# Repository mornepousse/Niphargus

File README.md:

<p align="center">
  <picture>
    <source media="(prefers-color-scheme: dark)" srcset="images/niphargus_logo_white.svg">
    
  </picture>
</p>

<h1 align="center">Niphargus</h1>

<p align="center">
  <em>The cave shrimp: blind, discreet, indestructible.</em><br>
  <em>La crevette des cavernes : aveugle, discrète, indestructible.</em>
</p>

---

## English

Niphargus is a thin, unkillable wireless split keyboard.

- **Two self-contained halves** — one ESP32-S3-WROOM-1 + nRF24L01+ and a 16340
  cell each, matrix scanning in deep sleep (RTC domain), the
  [KeSp dongle](https://github.com/mornepousse/KeSp_dongle) on the host side.
- **Wired fallback** — direct USB-C plus a TRRS jack between halves: *plugging it
  back in must be enough*. A 5 V handshake on the link makes hot-plug spark-free.
- **ESD hardening throughout** — TVS diodes on USB and TRRS, 100 Ω in series on
  every matrix line, careful ground planes. The static discharge you bring back
  to the keyboard will no longer crash it.
- **Sharp Memory LCD** (right half) for layer and battery status: holds its image
  at a few µA and never flickers. **Azoteq TPS43 trackpad** (left half), over I²C.
- **The survival kit** — an ESP32-P4 vault behind a CH334R USB hub: multi-ISO boot
  key, PGP token, storage. It only powers up when the keyboard is plugged in.

A complete redesign of the **Rouge-Gorge** (v1, 2022), a Jorne / Kyria rev2
derivative that was never built. This repository carries the full history:
Rouge-Gorge → rili → Niphargus.

**Status (2026-08)** — v2 schematic complete and reviewed, board routed, ERC and
DRC clean. Case in progress (see below). Firmware to follow.

## Français

Niphargus est un clavier split sans fil, fin et increvable.

- **Deux moitiés autonomes** — ESP32-S3-WROOM-1 + nRF24L01+ et une batterie 16340
  chacune, scan de la matrice en sommeil profond (domaine RTC),
  [dongle KeSp](https://github.com/mornepousse/KeSp_dongle) côté hôte.
- **Repli filaire** — USB-C direct et jack TRRS entre les moitiés : *rebrancher
  doit suffire*. Une poignée de main 5 V sur le lien évite les étincelles au branchement à chaud.
- **Robustesse ESD partout** — TVS sur USB et TRRS, 100 Ω série sur chaque ligne
  de matrice, plans de masse soignés. La décharge que vous ramenez au clavier ne
  le plantera plus.
- **Écran Sharp Memory LCD** (moitié droite) pour le calque et l'état des batteries :
  tient l'image à quelques µA sans jamais clignoter. **Trackpad Azoteq TPS43**
  (moitié gauche), en I²C.
- **La trousse de secours** — un coffre ESP32-P4 derrière un hub USB CH334R : clé
  bootable multi-ISO, token PGP, stockage. Il ne s'allume qu'en filaire.

Refonte complète du **Rouge-Gorge** (v1, 2022), un dérivé du Jorne et du Kyria
rev2 resté sur le papier. Le dépôt porte tout l'historique :
Rouge-Gorge → rili → Niphargus.

**État (2026-08)** — schéma v2 terminé et relu, carte routée, ERC et DRC au vert.
Boîtier en cours (ci-dessous). Firmware à suivre.

---

## Repository layout · Organisation du dépôt

| Path | Contents |
|---|---|
| `hardware/pcb/` | KiCad project — `niphar.kicad_pro` (schematic, board, footprints) |
| `hardware/order-*.csv` | Part orders: TME, LCSC, AliExpress |
| `hardware/kit-jlcpcb/` | Gerbers, BOM and CPL for JLCPCB |
| `case/` | Case generator and CAD output |
| `scripts/` | Anti-regression checks |
| `docs/` | Design specs and plans |

### Case · Boîtier

Three parts: a **CNC-machined 8.5 mm aluminium frame**, sandwiched between two
**2 mm polycarbonate plates**, 12.5 mm overall. The 16340 cell sits *beside* the
board, in a pocket milled into the frame itself.

Trois pièces : un **cadre aluminium usiné de 8,5 mm** pris entre deux **plaques
polycarbonate de 2 mm**, 12,5 mm hors tout. La 16340 se loge *à côté* de la carte,
dans une poche fraisée à même le cadre.

The frame outline is **not computed — it is drawn**. Edit `case/case_outline.svg`
(KiCad coordinates, 1 unit = 1 mm), then run:

Le contour du cadre n'est **pas calculé, il est dessiné**. Éditez
`case/case_outline.svg` (repère KiCad, 1 unité = 1 mm), puis lancez :

```sh
freecad --console case/gen_case.py
```

This regenerates the `.FCStd`, the STEP, the STL files and `case_plan.svg`.

### Anti-regression · Anti-régression

```sh
./scripts/check.sh --fast   # schematic ERC against the committed baseline
./scripts/check.sh          # + full board DRC
./scripts/install-hooks.sh  # once per clone: pre-push runs the full check
```

Green means *never more ERC/DRC errors or warnings than the committed baseline*
(`.tripwire-kicad-baseline`). CI is pinned to KiCad 10.0.4 with its own reference.

Vert signifie *jamais plus d'erreurs ni de warnings ERC/DRC que la référence
committée*. La CI est épinglée sur KiCad 10.0.4 avec sa propre référence.

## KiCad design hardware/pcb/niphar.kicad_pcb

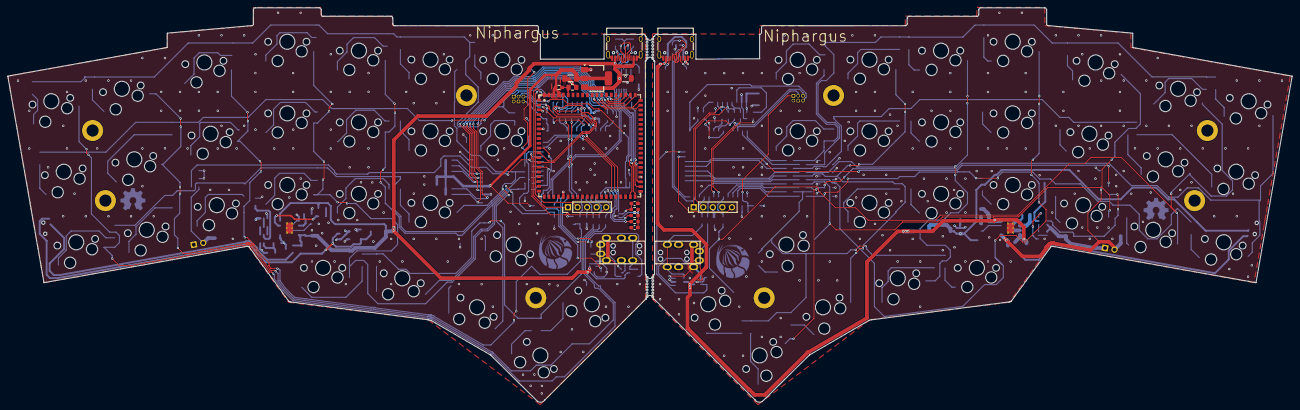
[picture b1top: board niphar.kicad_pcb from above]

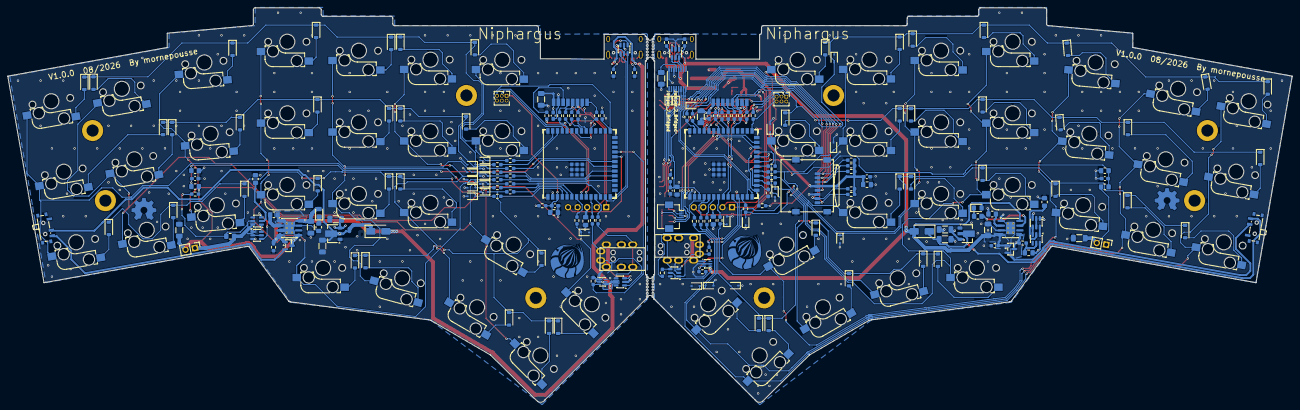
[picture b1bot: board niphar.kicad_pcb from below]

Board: 4 copper layers, 340.8 x 104.7 mm, 283 parts (206 on the bottom side), 208 nets.

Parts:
C1, C2, C5, C6, C7, C8, C17, C21, C22: 100nF; C_0603_1608Metric_Pad1.08x0.95mm_HandSolder
C3, C4, C9, C10, C14, C18, C27, C28: 1uF; C_0805_2012Metric_Pad1.18x1.45mm_HandSolder
C11, C12, C13, C15, C16, C19, C20, C23, C24, C25, C26, C29, C30: 10uF; C_1206_3216Metric_Pad1.33x1.80mm_HandSolder
D1, D2, D3, D4, D5, D6, D7, D8, D9, D10, D11, D12, D13, D14, D15, D16, D17, D18, D19, D20, D21, D22, D23, D24, D25, D26, D27, D28, D29, D30, D31, D32, D33, D34, D35, D36, D37, D38, D39, D40, D41, D42, D43, D44, D45, D46, D47, D48: D; D_SOD-123
D49, D50: LED; LED_0805_2012Metric_Pad1.15x1.40mm_HandSolder
D51, D52: SS14; D_SMA
D100, D101, D102, D103, D104, D105, D106, D107, D108, D109, D110, D111, D112, D113, D114, D115, D116, D117, D118, D119, D120, D121: SD05C-01F; D_SOD-323
H1, H2, H3, H4, H5, H6, H7, H8: MountingHole_Pad_MP; MountingHole_3.2mm_M3_DIN965_Pad
HS1, HS2: Heatsink_Pad; Niphargus_10mm_Cu
HS3: Heatsink_Pad; Niphargus_text_3mm_silk
J1, J2: Conn_02x03_Odd_Even; PinHeader_2x03_P1.27mm_Vertical
J3: TPS43_FPC; Hirose_FH12-6S-0.5SH_1x06-1MP_P0.50mm_Horizontal
J4, J12: Conn_01x05_Pin; PinHeader_1x05_P2.54mm_Vertical
J5, J6: AudioJack4; MJ-4PP-9_rev3
J7, J8: USB_C_Receptacle_USB2.0_16P; USB_C_Receptacle_HRO_TYPE-C-31-M-12
J9: Micro_SD_Card; microSD_HC_Wuerth_693072010801
J10, J11: Battery; PinHeader_1x02_P2.54mm_Vertical
JP1, JP2: Jumper_2_Bridged; Jumper
Q1, Q2: AO3407; SOT-23
Q3, Q4: FS8205; SOT-23-6
R1, R2, R33, R34, R48, R49, R54, R55, R56, R57, R58, R59: 10k; R_0603_1608Metric_Pad0.98x0.95mm_HandSolder
R3, R4, R5, R6, R7, R8, R9, R10, R11, R12, R13, R14, R15, R16, R17, R18, R19, R20, R21, R22, R23, R24, R25, R26, R27, R28, R30, R31, R36, R37, R38, R39, R40, R41, R44, R45, R46, R47, R70, R71: 100; R_0603_1608Metric_Pad0.98x0.95mm_HandSolder
R29, R32: 4.7k; R_0603_1608Metric_Pad0.98x0.95mm_HandSolder
R35, R42, R43, R60, R61: 100k; R_0603_1608Metric_Pad0.98x0.95mm_HandSolder
R50, R51, R52, R53: 5k1; R_0603_1608Metric_Pad0.98x0.95mm_HandSolder
R62, R63, R72, R73: 1k; R_0805_2012Metric_Pad1.20x1.40mm_HandSolder
R64, R65, R66, R67: 1M; R_0805_2012Metric_Pad1.20x1.40mm_HandSolder
R68, R69: 2k4; R_0805_2012Metric_Pad1.20x1.40mm_HandSolder
SW1, SW2, SW3, SW4, SW5, SW6, SW7, SW8, SW9, SW10, SW11, SW12, SW13, SW14, SW15, SW16, SW17, SW18, SW19, SW20, SW21, SW22, SW23, SW24, SW25, SW26, SW27, SW28, SW29, SW30, SW31, SW32, SW33, SW34, SW35, SW36, SW37, SW38, SW39, SW40, SW41, SW42, SW43, SW44, SW45, SW46, SW47, SW48, SW49, SW50, SW51, SW52: SW_PUSH; SW_Cherry_MX_1.00u_PCB
SW53, SW54: SW_SPDT; SW_SPDT_PCM12
U1, U2, U3, U4: D; D_SOD-123
U5, U6: ESP32-S3-WROOM-1; ESP32-S3-WROOM-1U
U7, U8: NRF24L01_Breakout; NRF24L01
U9, U10: SRV05-4; SOT-23-6
U11, U12: SiP32431DR3; SOT-363_SC-70-6
U13: CH334R; QSOP-16_3.9x4.9mm_P0.635mm
U14, U15: USBLC6-2SC6; SOT-23-6
U16: ESP32P4_QFN104; JC-ESP32P4-M3_V0.2
U17: AMS1117-3.3; SOT-223-3_TabPin2
U18, U19: TP4056-42-ESOP8; SOIC-8-1EP_3.9x4.9mm_P1.27mm_EP2.41x3.3mm_ThermalVias
U20, U21: HT7833; SOT-89-3
U22, U23: DW01A; SOT-23-6

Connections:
+3.3V: C6.1, C8.2, C9.2, C11.2, C26.2, J1.2, J3.4, J12.3, R2.2, R29.1, R32.1, R34.2, R35.1, U6.2 (3V3), U8.2 (VCC), U20.3 (VO)
+3.3V_D: C7.2, C10.2, C12.2, C25.2, J2.2, J4.3, R1.2, R33.2, U5.2 (3V3), U7.2 (VCC), U21.3 (VO)
+5V: C15.2, C20.2, D49.2 (A), D52.2 (A), J8.A4 (VBUS), J8.A9 (VBUS), J8.B4 (VBUS), J8.B9 (VBUS), Q2.1 (G), R60.2, U9.5 (VP), U12.4 (IN), U13.12 (V5), U14.5 (VBUS), U17.3 (VI), U18.4 (V_{CC}), U18.8 (CE)
+5V_D: C19.2, D50.2 (A), D51.2 (A), J7.A4 (VBUS), J7.A9 (VBUS), J7.B4 (VBUS), J7.B9 (VBUS), Q1.1 (G), R61.2, U10.5 (VP), U11.4 (IN), U15.5 (VBUS), U19.4 (V_{CC}), U19.8 (CE)
+BATT: C29.1, J10.2, Q2.3 (D), R64.1, R70.1, U18.5 (BAT)
+BATT_D: C30.1, J11.2, Q1.3 (D), R65.1, R71.1, U19.5 (BAT)
-BATT: C27.2, J10.1, Q4.1 (S1), U23.6 (GND)
-BATT_D: C28.2, J11.1, Q3.1 (S1), U22.6 (GND)
/P4/P4_3V3: C16.2, C17.2, C18.2, J9.4 (VDD), R48.2, R54.2, R55.1, R56.1, R57.1, R58.1, R59.1, U16.77 (ESP_3V3), U16.78 (ESP_3V3), U17.2 (VO)
/P4/SD_CLK: J9.5 (CLK), U16.63 (GPIO43)
/P4/SD_CMD: J9.3 (CMD), R57.2, U16.64 (GPIO44)
/P4/SD_DATA0: J9.7 (DAT0), R58.2, U16.59 (GPIO39)
/P4/SD_DATA1: J9.8 (DAT1), R59.2, U16.60 (GPIO40)
/P4/SD_DATA2: J9.1 (DAT2), R55.2, U16.61 (GPIO41)
/P4/SD_DATA3: J9.2 (DAT3/CD), R56.2, U16.62 (GPIO42)
/USB/DPU+: U13.11 (DPU+), U14.4 (I/O2)
/USB/DPU-: U13.10 (DMU-), U14.6 (I/O1)
/right/CE_1: R38.1, U5.8 (GPIO15/U0RTS/ADC2_CH4/XTAL_32K_P)
/right/CSN_1: R37.1, U5.9 (GPIO16/U0CTS/ADC2_CH5/XTAL_32K_N)
/right/CS_DPL: J4.5, U5.22 (GPIO14/TOUCH14/ADC2_CH3/FSPIWP/FSPIDQS/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)
/right/EN: C2.2, C4.2, J2.1, R1.1, U5.3 (EN)
/right/IO0: J2.6, R33.1, U5.27 (GPIO0/BOOT)
/right/IRQ_1: R40.1, U5.34 (MTDI/GPIO41/CLK_OUT1)
/right/LINK_5V_EN: R43.1, U5.23 (GPIO21), U11.3 (ON)
/right/LINK_RX: R44.2, U5.11 (GPIO18/U1RXD/ADC2_CH7/CLK_OUT3)
/right/LINK_TX: R46.2, U5.10 (GPIO17/U1TXD/ADC2_CH6)
/right/MISO: R15.2, U7.7 (MISO)
/right/MOSI: J4.1, R17.2, U7.6 (MOSI)
/right/RX: J2.5, U5.36 (U0RXD/GPIO44/CLK_OUT2)
/right/SCK: J4.2, R31.2, U7.5 (SCK)
/right/TIP_5V: J5.T, U10.3 (IO2), U11.1 (OUT)
/right/TX: J2.3, U5.37 (U0TXD/GPIO43/CLK_OUT1)
/right/col0: R12.2, U5.6 (GPIO6/TOUCH6/ADC1_CH5)
/right/col1: R13.2, U5.7 (GPIO7/TOUCH7/ADC1_CH6)
/right/col2: R19.2, U5.12 (GPIO8/TOUCH8/ADC1_CH7/SUBSPICS1)
/right/col3: R22.2, U5.17 (GPIO9/TOUCH9/ADC1_CH8/FSPIHD/SUBSPIHD)
/right/col4: R24.2, U5.19 (GPIO11/TOUCH11/ADC2_CH0/FSPID/FSPIIO5/S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)
/right/col5: R26.2, U5.18 (GPIO10/TOUCH10/ADC1_CH9/FSPICS0/FSPIIO4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)
/right/col6: R28.2, U5.39 (GPIO1/TOUCH1/ADC1_CH0)
/right/row0: R3.1, U5.38 (GPIO2/TOUCH2/ADC1_CH1)
/right/row1: R5.1, U5.20 (GPIO12/TOUCH12/ADC2_CH1/FSPICLK/FSPIIO6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)
/right/row2: R8.1, U5.4 (GPIO4/TOUCH4/ADC1_CH3)
/right/row3: R10.1, U5.5 (GPIO5/TOUCH5/ADC1_CH4)
/s3/CE_1: R39.1, U6.8 (GPIO15/U0RTS/ADC2_CH4/XTAL_32K_P)
/s3/CSN_1: R36.1, U6.9 (GPIO16/U0CTS/ADC2_CH5/XTAL_32K_N)
/s3/CS_DPL: J12.5, U6.22 (GPIO14/TOUCH14/ADC2_CH3/FSPIWP/FSPIDQS/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)
/s3/EN: C1.2, C3.2, J1.1, R2.1, U6.3 (EN)
/s3/IO0: J1.6, R34.1, U6.27 (GPIO0/BOOT)
/s3/IRQ_1: R41.1, U6.34 (MTDI/GPIO41/CLK_OUT1)
/s3/LINK_5V_EN: R42.1, U6.23 (GPIO21), U12.3 (ON)
/s3/LINK_RX: R45.2, U6.11 (GPIO18/U1RXD/ADC2_CH7/CLK_OUT3)
/s3/LINK_TX: R47.2, U6.10 (GPIO17/U1TXD/ADC2_CH6)
/s3/RX: J1.5, U6.36 (U0RXD/GPIO44/CLK_OUT2)
/s3/TIP_5V: J6.T, U9.3 (IO2), U12.1 (OUT)
/s3/TP_NRST: C5.1, J3.2, R35.2
/s3/TP_RDY: J3.1, U6.35 (MTMS/GPIO42)
/s3/TP_SCL: J3.5, R32.2, U6.25 (GPIO48/SPICLK_N/SUBSPICLK_N_DIFF)
/s3/TP_SDA: J3.6, R29.2, U6.24 (GPIO47/SPICLK_P/SUBSPICLK_P_DIFF)
/s3/TX: J1.3, U6.37 (U0TXD/GPIO43/CLK_OUT1)
/s3/col0: R11.2, U6.4 (GPIO4/TOUCH4/ADC1_CH3)
/s3/col1: R14.2, U6.5 (GPIO5/TOUCH5/ADC1_CH4)
/s3/col2: R20.2, U6.7 (GPIO7/TOUCH7/ADC1_CH6)
/s3/col3: R21.2, U6.17 (GPIO9/TOUCH9/ADC1_CH8/FSPIHD/SUBSPIHD)
/s3/col4: R23.2, U6.18 (GPIO10/TOUCH10/ADC1_CH9/FSPICS0/FSPIIO4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)
/s3/col5: R25.2, U6.19 (GPIO11/TOUCH11/ADC2_CH0/FSPID/FSPIIO5/S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)
/s3/col6: R27.2, U6.20 (GPIO12/TOUCH12/ADC2_CH1/FSPICLK/FSPIIO6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)
/s3/row0: R4.1, U6.39 (GPIO1/TOUCH1/ADC1_CH0)
/s3/row1: R6.1, U6.38 (GPIO2/TOUCH2/ADC1_CH1)
/s3/row2: R7.1, U6.12 (GPIO8/TOUCH8/ADC1_CH7/SUBSPICS1)
/s3/row3: R9.1, U6.6 (GPIO6/TOUCH6/ADC1_CH5)
CS_P4: R48.1, U6.15 (GPIO3/TOUCH3/ADC1_CH2), U16.11 (GPIO7)
D+_p4: U13.6 (DP2+), U16.40 (ESP_USB_P)
D+_s3: U6.14 (GPIO20/U1CTS/ADC2_CH9/CLK_OUT1/USB_D+), U13.8 (DP1+)
D+_s3_d: U5.14 (GPIO20/U1CTS/ADC2_CH9/CLK_OUT1/USB_D+), U15.4 (I/O2)
D-_p4: U13.5 (DM2-), U16.39 (ESP_USB_N)
D-_s3: U6.13 (GPIO19/U1RTS/ADC2_CH8/CLK_OUT2/USB_D-), U13.7 (DM1-)
D-_s3_d: U5.13 (GPIO19/U1RTS/ADC2_CH8/CLK_OUT2/USB_D-), U15.6 (I/O1)
GND: C1.1, C2.1, C3.1, C4.1, C5.2, C6.2, C7.1, C8.1, C9.1, C10.1, C11.1, C12.1, C13.2, C14.1, C15.1, C16.1, C17.1, C18.1, C19.1, C20.1, C21.1, C22.1, C23.1, C24.1, C25.1, C26.1, C29.2, C30.2, D100.2 (A2), D101.2 (A2), D102.2 (A2), D103.2 (A2), D104.2 (A2), D105.2 (A2), D106.2 (A2), D107.1 (A1), D108.1 (A1), D109.1 (A1), D110.1 (A1), D111.2 (A2), D112.2 (A2), D113.2 (A2), D114.2 (A2), D115.2 (A2), D116.2 (A2), D117.2 (A2), D118.2 (A2), D119.2 (A2), D120.2 (A2), D121.2 (A2), J1.4, J2.4, J3.3, J4.4, J5.S, J6.S, J7.A1 (GND), J7.A12 (GND), J7.B1 (GND), J7.B12 (GND), J7.SH (SHIELD), J8.A1 (GND), J8.A12 (GND), J8.B1 (GND), J8.B12 (GND), J8.SH (SHIELD), J9.6 (VSS), J9.SH (SHIELD), J12.4, Q3.3 (S2), Q4.3 (S2), R42.2, R43.2, R49.1, R50.2, R51.2, R52.1, R53.1, R60.1, R61.1, R66.2, R67.2, R68.2, R69.2, R72.2, R73.2, U5.1 (GND), U5.40 (GND), U5.41 (GND), U6.1 (GND), U6.40 (GND), U6.41 (GND), U7.1 (GND), U8.1 (GND), U9.2 (VN), U10.2 (VN), U11.2 (GND), U11.5 (GND), U12.2 (GND), U12.5 (GND), U13.14 (GND), U13.16 (XI), U14.2 (GND), U15.2 (GND), U16.1 (GND), U16.3 (GND), U16.7 (GND), U16.25 (GND), U16.32 (GND), U16.41 (GND), U16.44 (GND), U16.79 (GND), U16.80 (GND), U17.1 (GND), U18.1 (TEMP), U18.3 (GND), U18.9 (EPAD), U19.1 (TEMP), U19.3 (GND), U19.9 (EPAD), U20.1 (GND), U21.1 (GND)
IRQ_P4: R49.2, U6.16 (GPIO46), U16.15 (GPIO11)
J_PROG_P4_N: JP2.2 (B), U13.3 (DM3-)
J_PROG_P4_P: JP1.2 (B), U13.4 (DP3+)
MISO_L: R16.2, U8.7 (MISO), U16.14 (GPIO10)
MOSI_L: J12.1, R18.2, U8.6 (MOSI), U16.12 (GPIO8)
unnamed: D1.2 (A), SW2.2
unnamed: D1.1 (K), D10.1 (K), D15.1 (K), D22.1 (K), D29.1 (K), D37.1 (K), D45.1 (K), D118.1 (A1), R3.2
unnamed: D2.2 (A), SW1.2
unnamed: D3.2 (A), SW3.2
unnamed: D4.2 (A), SW4.2
unnamed: D5.2 (A), SW6.2
unnamed: D6.2 (A), SW5.2
unnamed: D7.2 (A), SW7.2
unnamed: D8.2 (A), SW8.2
unnamed: D9.2 (A), SW10.2
unnamed: D10.2 (A), SW9.2
unnamed: D11.2 (A), SW12.2
unnamed: D12.2 (A), SW11.2
unnamed: D13.2 (A), SW14.2
unnamed: D14.2 (A), SW13.2
unnamed: D15.2 (A), SW18.2
unnamed: D16.2 (A), SW17.2
unnamed: D17.2 (A), SW20.2
unnamed: D18.2 (A), SW19.2
unnamed: D19.2 (A), SW22.2
unnamed: D20.2 (A), SW21.2
unnamed: D21.2 (A), SW26.2
unnamed: D22.2 (A), SW25.2
unnamed: D23.2 (A), SW28.2
unnamed: D24.2 (A), SW27.2
unnamed: D25.2 (A), SW29.2
unnamed: D26.2 (A), SW30.2
unnamed: D27.2 (A), SW32.2
unnamed: D28.2 (A), SW31.2
unnamed: D29.2 (A), SW34.2
unnamed: D30.2 (A), SW33.2
unnamed: D31.2 (A), SW36.2
unnamed: D32.2 (A), SW35.2
unnamed: D33.2 (A), SW38.2
unnamed: D34.2 (A), SW37.2
unnamed: D35.2 (A), SW39.2
unnamed: D36.2 (A), SW40.2
unnamed: D37.2 (A), SW42.2
unnamed: D38.2 (A), SW41.2
unnamed: D39.2 (A), SW44.2
unnamed: D40.2 (A), SW43.2
unnamed: D41.2 (A), SW45.2
unnamed: D42.2 (A), SW46.2
unnamed: D43.2 (A), SW47.2
unnamed: D44.2 (A), SW48.2
unnamed: D45.2 (A), SW50.2
unnamed: D46.2 (A), SW49.2
unnamed: D47.2 (A), SW51.2
unnamed: D48.2 (A), SW52.2
unnamed: D49.1 (K), R62.1
unnamed: D50.1 (K), R63.1
unnamed: C23.2, D51.1 (K), SW53.2 (B), U21.2 (VI)
unnamed: C24.2, D52.1 (K), SW54.3 (C), U20.2 (VI)
unnamed: D100.1 (A1), R11.1, SW1.1, SW3.1, SW5.1, SW8.1
unnamed: D101.1 (A1), R14.1, SW10.1, SW12.1, SW14.1, SW15.1
unnamed: D102.1 (A1), R20.1, SW17.1, SW19.1, SW21.1, SW24.1
unnamed: D103.1 (A1), R21.1, SW26.1, SW27.1, SW30.1, SW31.1
unnamed: D104.1 (A1), R23.1, SW33.1, SW35.1, SW38.1, SW40.1
unnamed: D105.1 (A1), R25.1, SW41.1, SW43.1, SW45.1, SW47.1
unnamed: D106.1 (A1), R27.1, SW49.1, SW52.1
unnamed: D2.1 (K), D9.1 (K), D16.1 (K), D21.1 (K), D30.1 (K), D38.1 (K), D46.1 (K), D107.2 (A2), R4.2
unnamed: D3.1 (K), D11.1 (K), D18.1 (K), D24.1 (K), D32.1 (K), D40.1 (K), D48.1 (K), D108.2 (A2), R6.2
unnamed: D6.1 (K), D13.1 (K), D20.1 (K), D26.1 (K), D33.1 (K), D41.1 (K), D109.2 (A2), R7.2
unnamed: D8.1 (K), D28.1 (K), D36.1 (K), D43.1 (K), D110.2 (A2), R9.2, U2.1 (K), U3.1 (K)
unnamed: D111.1 (A1), R12.1, SW2.1, SW4.1, SW6.1, SW7.1
unnamed: D112.1 (A1), R13.1, SW9.1, SW11.1, SW13.1, SW16.1
unnamed: D113.1 (A1), R19.1, SW18.1, SW20.1, SW22.1, SW23.1
unnamed: D114.1 (A1), R22.1, SW25.1, SW28.1, SW29.1, SW32.1
unnamed: D115.1 (A1), R24.1, SW34.1, SW36.1, SW37.1, SW39.1
unnamed: D116.1 (A1), R26.1, SW42.1, SW44.1, SW46.1, SW48.1
unnamed: D117.1 (A1), R28.1, SW50.1, SW51.1
unnamed: D4.1 (K), D12.1 (K), D17.1 (K), D23.1 (K), D31.1 (K), D39.1 (K), D47.1 (K), D119.1 (A1), R5.2
unnamed: D5.1 (K), D14.1 (K), D19.1 (K), D25.1 (K), D34.1 (K), D42.1 (K), D120.1 (A1), R8.2
unnamed: D7.1 (K), D27.1 (K), D35.1 (K), D44.1 (K), D121.1 (A1), R10.2, U1.1 (K), U4.1 (K)
unnamed: J7.A5 (CC1), R51.1
unnamed: J7.B5 (CC2), R53.2
unnamed: J7.A6 (D+), J7.B6 (D+), U15.3 (I/O2)
unnamed: J7.A7 (D-), J7.B7 (D-), U15.1 (I/O1)
unnamed: J8.A5 (CC1), R50.1
unnamed: J8.B5 (CC2), R52.2
unnamed: J8.A6 (D+), J8.B6 (D+), U14.3 (I/O2)
unnamed: J8.A7 (D-), J8.B7 (D-), U14.1 (I/O1)
unnamed: JP1.1 (A), U16.43 (USB1_P1_P)
unnamed: JP2.1 (A), U16.42 (USB1_P1_N)
unnamed: Q1.2 (S), SW53.3 (C)
unnamed: Q2.2 (S), SW54.2 (B)
unnamed: Q3.2 (D12), Q3.5 (D12)
unnamed: Q3.6 (G1), U22.1 (OD)
unnamed: Q3.4 (G2), U22.3 (OC)
unnamed: Q4.2 (D12), Q4.5 (D12)
unnamed: Q4.6 (G1), U23.1 (OD)
unnamed: Q4.4 (G2), U23.3 (OC)
unnamed: SW16.2, U1.2 (A)
unnamed: SW15.2, U2.2 (A)
unnamed: SW24.2, U3.2 (A)
unnamed: SW23.2, U4.2 (A)
unnamed: R31.1, U5.31 (GPIO38/FSPIWP/SUBSPIWP)
unnamed: R15.1, U5.32 (MTCK/GPIO39/CLK_OUT3/SUBSPICS1)
unnamed: R17.1, U5.33 (MTDO/GPIO40/CLK_OUT2)
unnamed: R30.1, U6.31 (GPIO38/FSPIWP/SUBSPIWP)
unnamed: R16.1, U6.32 (MTCK/GPIO39/CLK_OUT3/SUBSPICS1)
unnamed: R18.1, U6.33 (MTDO/GPIO40/CLK_OUT2)
unnamed: R38.2, U7.3 (CE)
unnamed: R40.2, U7.8 (IRQ)
unnamed: R37.2, U7.4 (~CSN)
unnamed: R39.2, U8.3 (CE)
unnamed: R41.2, U8.8 (IRQ)
unnamed: R36.2, U8.4 (~CSN)
unnamed: J6.R2, R47.1, U9.1 (IO1)
unnamed: J6.R1, R45.1, U9.4 (IO3)
unnamed: J5.R2, R46.1, U10.1 (IO1)
unnamed: J5.R1, R44.1, U10.4 (IO3)
unnamed: C13.1, U13.13 (VDD33_{LDO})
unnamed: C14.2, R54.1, U16.75 (CHIP_PU)
unnamed: R68.1, U18.2 (PROG)
unnamed: R62.2, U18.7 (~CHRG)
unnamed: R69.1, U19.2 (PROG)
unnamed: R63.2, U19.7 (~CHRG)
unnamed: R72.1, U22.2 (CS)
unnamed: C28.1, R71.2, U22.5 (VCC)
unnamed: R73.1, U23.2 (CS)
unnamed: C27.1, R70.2, U23.5 (VCC)
SCK_L: J12.2, R30.2, U8.5 (SCK), U16.13 (GPIO9)
VBAT_SENSE: C21.2, R64.2, R67.1, U6.21 (GPIO13/TOUCH13/ADC2_CH2/FSPIQ/FSPIIO7/S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)
VBAT_SENSE_d: C22.2, R65.2, R66.1, U5.21 (GPIO13/TOUCH13/ADC2_CH2/FSPIQ/FSPIIO7/S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)
